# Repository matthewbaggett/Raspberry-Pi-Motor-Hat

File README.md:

Raspberry-Pi-Motor-Hat
======================

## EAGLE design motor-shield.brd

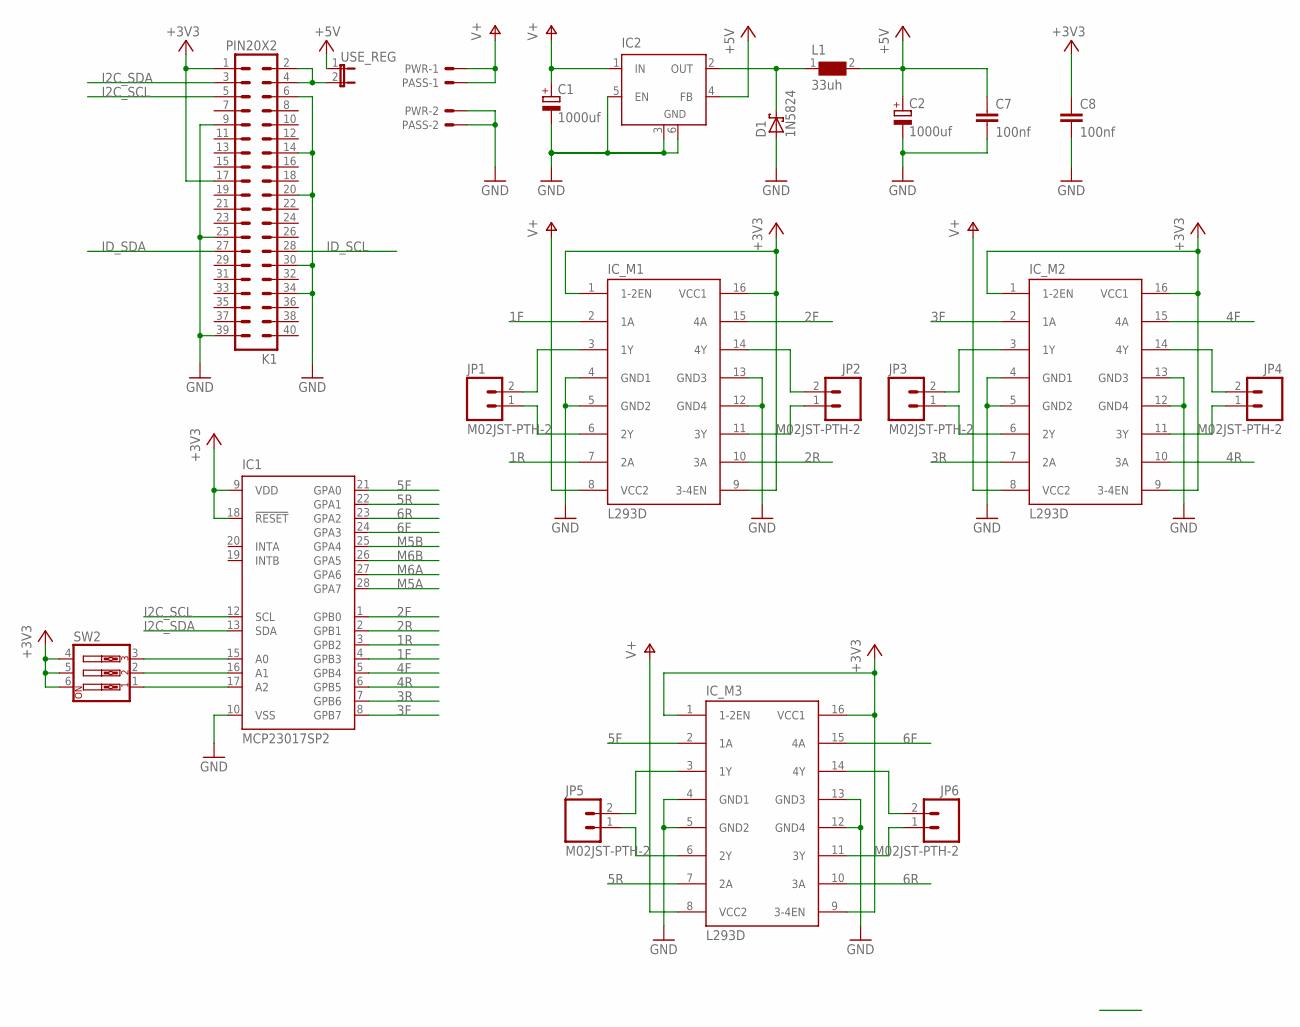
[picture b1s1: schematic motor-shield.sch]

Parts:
C1: 1000uf; E2,5-6
C2: 1000uf; E2,5-7
C7, C8: 100nf; C025-030X050
D1: 1N5824; DO41-7.6
IC1: MCP23017SP2; DIL28-3-ROUND
IC2: LM2596S; TO263-5
IC_M1, IC_M2, IC_M3: L293D; DIL16
JP1, JP2, JP3, JP4, JP5, JP6: M02JST-PTH-2; JST-2-PTH
K1: PIN20X2; PIN_20X2
L1: 33uh; WE-PD_1260/1245/1280/1210
PASS: 22-05-7028-02; 7395-02
PWR: 22-05-7028-02; 7395-02
SW2: SW_DIP-3; EDG-03
USE_REG: JP1E; JP1

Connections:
1F: IC1.4 (GPB3), IC_M1.2 (1A)
1R: IC1.3 (GPB2), IC_M1.7 (2A)
2F: IC1.1 (GPB0), IC_M1.15 (4A)
2R: IC1.2 (GPB1), IC_M1.10 (3A)
3F: IC1.8 (GPB7), IC_M2.2 (1A)
3R: IC1.7 (GPB6), IC_M2.7 (2A)
4F: IC1.5 (GPB4), IC_M2.15 (4A)
4R: IC1.6 (GPB5), IC_M2.10 (3A)
5F: IC1.21 (GPA0), IC_M3.2 (1A)
5R: IC1.22 (GPA1), IC_M3.7 (2A)
6F: IC1.24 (GPA3), IC_M3.15 (4A)
6R: IC1.23 (GPA2), IC_M3.10 (3A)
+3V3: C8.1, IC1.9 (VDD), IC1.18 (!RESET), IC_M1.1 (1-2EN), IC_M1.9 (3-4EN), IC_M1.16 (VCC1), IC_M2.1 (1-2EN), IC_M2.9 (3-4EN), IC_M2.16 (VCC1), IC_M3.1 (1-2EN), IC_M3.9 (3-4EN), IC_M3.16 (VCC1), K1.1, K1.17, SW2.4, SW2.5, SW2.6
+5V: C2.+, C7.1, IC2.4 (FB), L1.2, USE_REG.1
GND: C1.-, C2.-, C7.2, C8.2, D1.A, IC1.10 (VSS), IC2.3 (GND), IC2.5 (EN), IC2.6 (GND), IC_M1.4 (GND1), IC_M1.5 (GND2), IC_M1.12 (GND4), IC_M1.13 (GND3), IC_M2.4 (GND1), IC_M2.5 (GND2), IC_M2.12 (GND4), IC_M2.13 (GND3), IC_M3.4 (GND1), IC_M3.5 (GND2), IC_M3.12 (GND4), IC_M3.13 (GND3), K1.6, K1.9, K1.14, K1.20, K1.25, K1.30, K1.34, K1.39, PASS.2, PWR.2
I2C_SCL: IC1.12 (SCL), K1.5
I2C_SDA: IC1.13 (SDA), K1.3
ID_SCL: K1.28
ID_SDA: K1.27
M5A: IC1.28 (GPA7)
M5B: IC1.25 (GPA4)
M6A: IC1.27 (GPA6)
M6B: IC1.26 (GPA5)
unnamed: IC_M2.11 (3Y), JP4.1
unnamed: IC1.15 (A0), SW2.3
unnamed: IC1.16 (A1), SW2.2
unnamed: IC_M2.14 (4Y), JP4.2
unnamed: IC_M1.11 (3Y), JP2.1
unnamed: IC_M1.14 (4Y), JP2.2
unnamed: IC_M1.6 (2Y), JP1.1
unnamed: IC_M1.3 (1Y), JP1.2
unnamed: IC_M2.6 (2Y), JP3.1
unnamed: IC_M2.3 (1Y), JP3.2
unnamed: IC_M3.11 (3Y), JP6.1
unnamed: IC_M3.14 (4Y), JP6.2
unnamed: IC_M3.6 (2Y), JP5.1
unnamed: K1.2, K1.4, USE_REG.2
unnamed: IC_M3.3 (1Y), JP5.2
unnamed: IC1.17 (A2), SW2.1
V+: C1.+, IC2.1 (IN), IC_M1.8 (VCC2), IC_M2.8 (VCC2), IC_M3.8 (VCC2), PASS.1, PWR.1
VOUT: D1.C, IC2.2 (OUT), L1.1

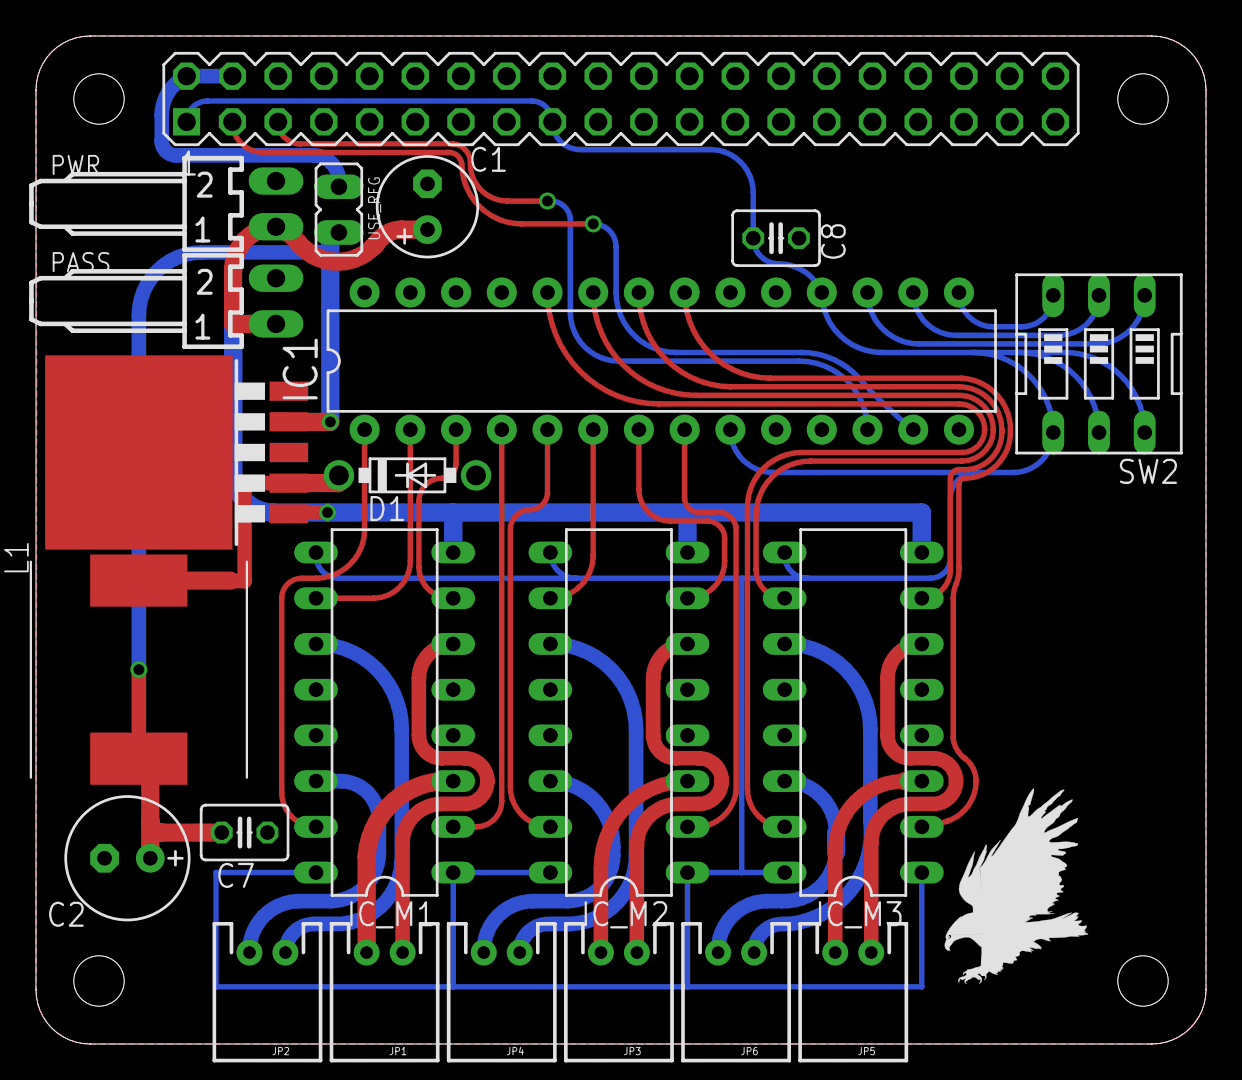
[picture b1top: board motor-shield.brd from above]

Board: 2 copper layers, 65.0 x 56.0 mm, 23 parts (0 on the bottom side), 35 nets.

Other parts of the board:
U$1: EAGLE-PLC-8MM

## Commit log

2014-08-01 Complete, no air wires, passes DRC
2014-08-01 Initial commit, after forking from Raspberry-Pi-Servo-Hat and removing servo-related parts. Keeping the huge regulator though.
2014-08-01 Adding more to the gitignore
2014-09-07 Rebuilt to match servo shield
2014-09-07 ROTATE THE EAGLE

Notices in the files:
parts and their libraries:
SparkFun-Connectors: Licensing: Creative Commons ShareAlike 4.0 International - https://creativecommons.org/licenses/by-sa/4.0
